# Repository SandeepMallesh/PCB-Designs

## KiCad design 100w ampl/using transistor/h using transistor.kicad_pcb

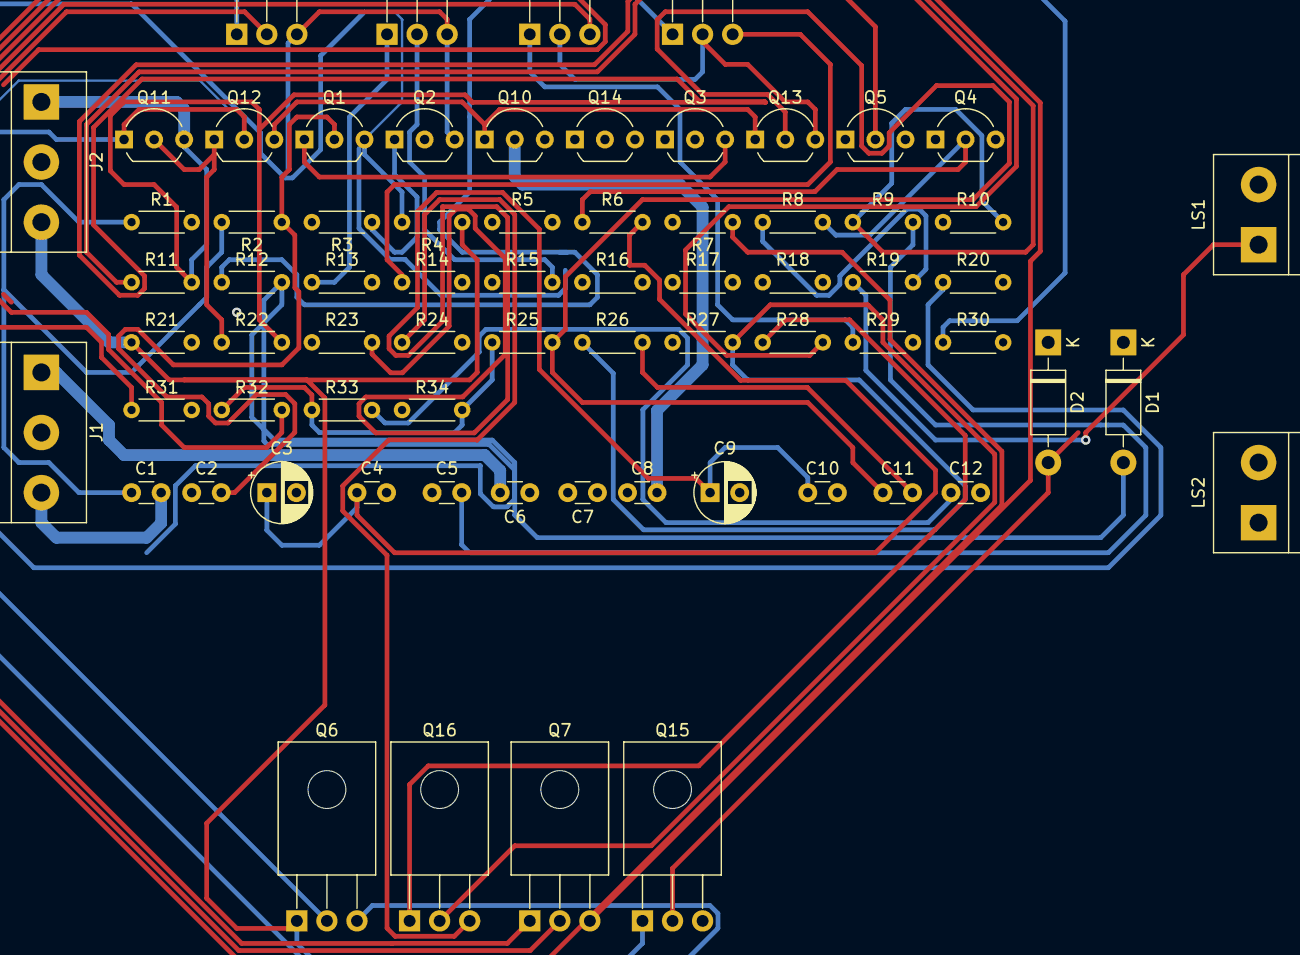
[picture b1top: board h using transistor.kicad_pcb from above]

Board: 2 copper layers, 70 parts (0 on the bottom side), 47 nets.

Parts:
C1, C6: 470n; C_Disc_D3.0mm_W1.6mm_P2.50mm
C2, C8: 470pf; C_Disc_D3.0mm_W1.6mm_P2.50mm
C3, C9: 47u; CP_Radial_D5.0mm_P2.50mm
C4, C7, C10, C12: 100n; C_Disc_D3.0mm_W1.6mm_P2.50mm
C5, C11: 100pf; C_Disc_D3.0mm_W1.6mm_P2.50mm
D1, D2: 1N4002; D_DO-41_SOD81_P10.16mm_Horizontal
J1: R G L; TerminalBlock_bornier-3_P5.08mm
J2: PWR; TerminalBlock_bornier-3_P5.08mm
LS1, LS2: Speaker; TerminalBlock_bornier-2_P5.08mm
Q1, Q3, Q4, Q10, Q12, Q13: MPSA43; TO-92_Inline_Wide
Q2, Q5, Q11, Q14: BC546; TO-92_Inline_Wide
Q6, Q15: MJE350; TO-126_Horizontal
Q7, Q16: MJE340; TO-126_Horizontal
Q8, Q17: IRFP244; TO-220-3_Horizontal
Q9, Q18: IRFP9240; TO-220-3_Horizontal
R1, R16: 47k; R_Axial_DIN0204_L3.6mm_D1.6mm_P5.08mm_Horizontal
R2, R18: 4.7k; R_Axial_DIN0204_L3.6mm_D1.6mm_P5.08mm_Horizontal
R3, R20: 22k; R_Axial_DIN0204_L3.6mm_D1.6mm_P5.08mm_Horizontal
R4, R21: 1k; R_Axial_DIN0204_L3.6mm_D1.6mm_P5.08mm_Horizontal
R5, R12, R13, R22, R29, R30: 330; R_Axial_DIN0204_L3.6mm_D1.6mm_P5.08mm_Horizontal
R6, R23: 1.5k; R_Axial_DIN0204_L3.6mm_D1.6mm_P5.08mm_Horizontal
R7, R24: 15k; R_Axial_DIN0204_L3.6mm_D1.6mm_P5.08mm_Horizontal
R8, R25: 33k; R_Axial_DIN0204_L3.6mm_D1.6mm_P5.08mm_Horizontal
R9, R26: 150k; R_Axial_DIN0204_L3.6mm_D1.6mm_P5.08mm_Horizontal
R10, R27: 390; R_Axial_DIN0204_L3.6mm_D1.6mm_P5.08mm_Horizontal
R11, R28: 39; R_Axial_DIN0204_L3.6mm_D1.6mm_P5.08mm_Horizontal
R14, R15, R31, R32: 0R33; R_Axial_DIN0204_L3.6mm_D1.6mm_P5.08mm_Horizontal
R17, R33: 10; R_Axial_DIN0204_L3.6mm_D1.6mm_P5.08mm_Horizontal
R19, R34: 220; R_Axial_DIN0204_L3.6mm_D1.6mm_P5.08mm_Horizontal

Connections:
GND: C2.1, C3.2, C4.2, C7.2, C8.1, C9.2, C10.2, C12.2, J1.2, J2.2, LS1.2, LS2.2, R1.2, R3.2, R7.2, R16.2, R20.2, R24.2
unnamed: C1.1, R1.1, R2.2
unnamed: C1.2, J1.3
unnamed: C2.2, Q1.2, R2.1
unnamed: C3.1, C4.1, R6.2
unnamed: C5.1, Q4.2, R6.1, R8.2
unnamed: C5.2, R9.2
unnamed: C6.1, R16.1, R18.2
unnamed: C6.2, J1.1
unnamed: C7.1, R17.2
unnamed: C8.2, Q10.2, R18.1
unnamed: C9.1, C10.1, R23.2
unnamed: C11.1, Q13.2, R23.1, R25.2
unnamed: C11.2, R26.2
unnamed: C12.1, R33.2
unnamed: D1.1, R10.1
unnamed: D1.2, Q6.2, R12.2
unnamed: D2.1, R27.1
unnamed: D2.2, Q15.2, R29.2
unnamed: LS1.1, R19.1
unnamed: LS2.1, R34.1
unnamed: Q1.1, Q3.3, Q4.1
unnamed: Q1.3, Q6.3, R4.2
unnamed: Q2.1, Q3.2, R3.1
unnamed: Q2.2, Q3.1, R5.1
unnamed: Q5.2, Q7.1, R11.1
unnamed: Q5.3, Q7.3, R7.1
unnamed: Q7.2, R9.1, R10.2, R13.2
unnamed: Q8.1, R12.1
unnamed: Q8.3, R14.1
unnamed: Q9.1, R13.1
unnamed: Q9.2, R15.2
unnamed: Q10.1, Q12.3, Q13.1
unnamed: Q10.3, Q15.3, R21.2
unnamed: Q11.1, Q12.2, R20.1
unnamed: Q11.2, Q12.1, R22.1
unnamed: Q14.2, Q16.1, R28.1
unnamed: Q14.3, Q16.3, R24.1
unnamed: Q16.2, R26.1, R27.2, R30.2
unnamed: Q17.1, R29.1
unnamed: Q17.3, R31.1
unnamed: Q18.1, R30.1
unnamed: Q18.2, R32.2
unnamed: R8.1, R14.2, R15.1, R17.1, R19.2
unnamed: R25.1, R31.2, R32.1, R33.1, R34.2
VCC: J2.3, Q4.3, Q6.1, Q8.2, Q13.3, Q15.1, Q17.2, R4.1, R21.1
VSS: J2.1, Q2.3, Q5.1, Q9.3, Q11.3, Q14.1, Q18.3, R5.2, R11.2, R22.2, R28.2

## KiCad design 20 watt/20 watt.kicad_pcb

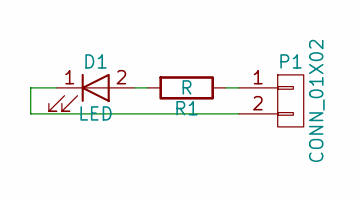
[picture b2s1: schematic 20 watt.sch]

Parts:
D1: LED; LED_D5.0mm_FlatTop
P1: CONN_01X02; SL-102-X-XX_1x02
R1: R; R_Axial_DIN0204_L3.6mm_D1.6mm_P5.08mm_Horizontal

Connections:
unnamed: D1.1 (K), P1.2
unnamed: D1.2 (A), R1.2
unnamed: P1.1, R1.1

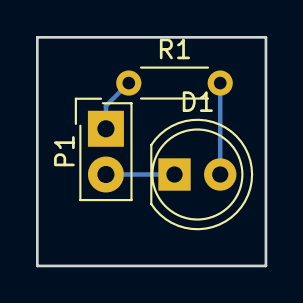
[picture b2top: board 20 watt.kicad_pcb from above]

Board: 2 copper layers, 12.7 x 12.7 mm, 3 parts (0 on the bottom side), 3 nets.

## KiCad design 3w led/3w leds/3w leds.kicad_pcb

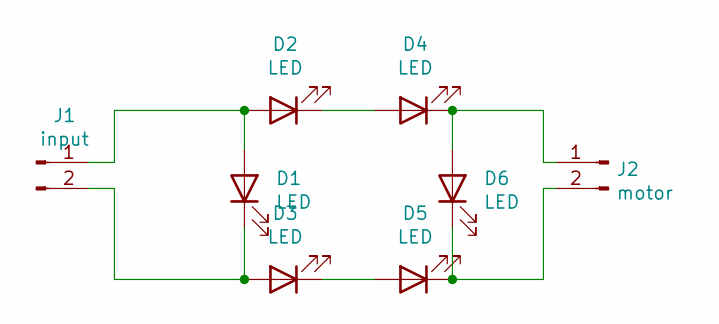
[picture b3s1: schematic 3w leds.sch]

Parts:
D1, D2, D3, D4, D5, D6: LED; LED_1W_3W_R8
J1: input; JWT_A3963_1x02_P3.96mm_Vertical
J2: motor; JWT_A3963_1x02_P3.96mm_Vertical

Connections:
unnamed: D1.1 (K), D3.2 (A), J1.2
unnamed: D1.2 (A), D2.2 (A), J1.1
unnamed: D2.1 (K), D4.2 (A)
unnamed: D3.1 (K), D5.2 (A)
unnamed: D4.1 (K), D6.2 (A), J2.1
unnamed: D5.1 (K), D6.1 (K), J2.2

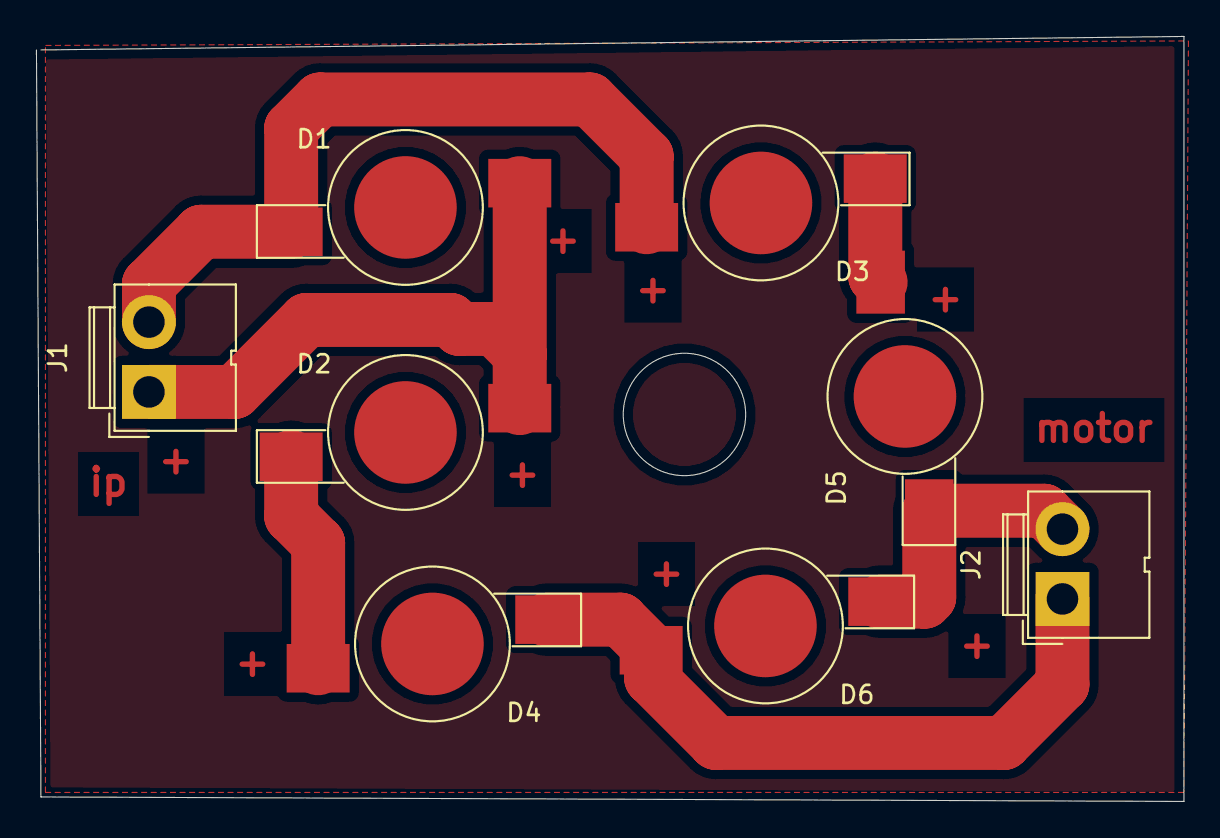
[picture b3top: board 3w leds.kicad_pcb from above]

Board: 2 copper layers, 63.8 x 42.5 mm, 8 parts (0 on the bottom side), 6 nets.

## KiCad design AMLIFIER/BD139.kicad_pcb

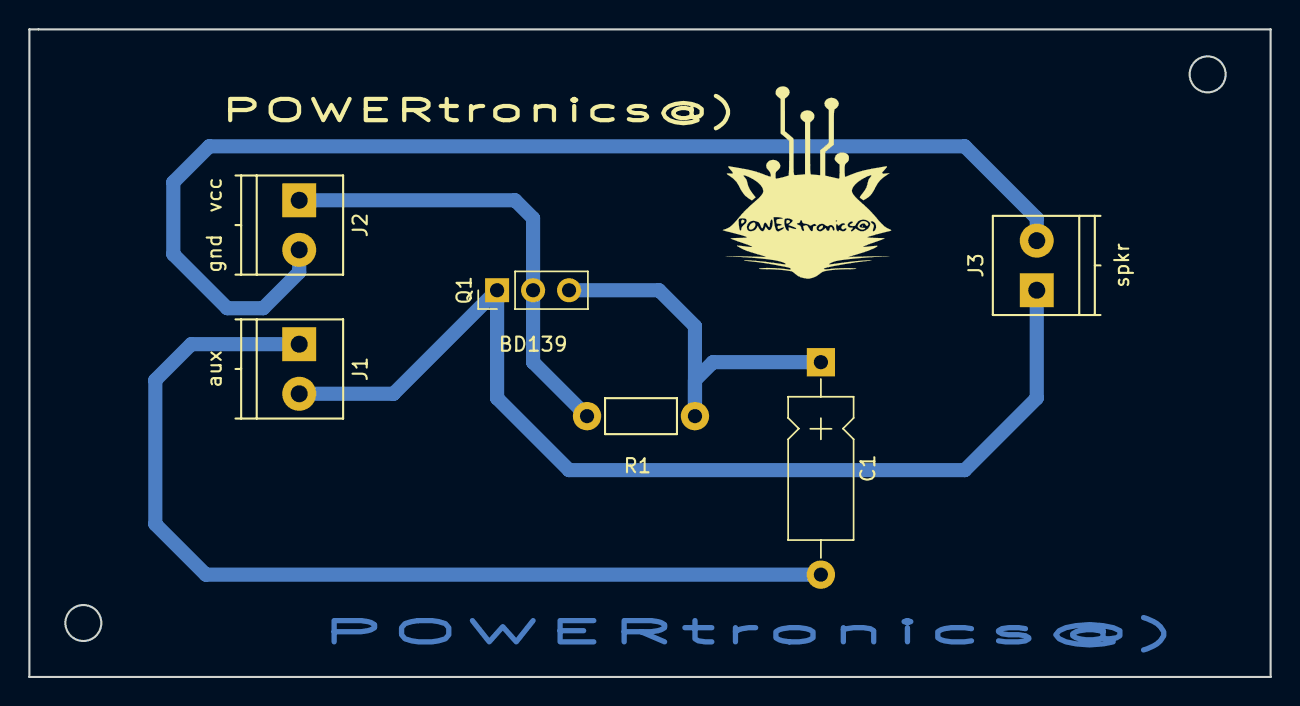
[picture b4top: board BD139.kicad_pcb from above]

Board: 2 copper layers, 87.6 x 45.7 mm, 6 parts (0 on the bottom side), 5 nets.

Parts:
C1: CP; CP_Axial_L10.0mm_D4.5mm_P15.00mm_Horizontal
J1: aux; TerminalBlock_Pheonix_PT-3.5mm_2pol
J2: gnd vcc; TerminalBlock_Pheonix_PT-3.5mm_2pol
J3: spkr; TerminalBlock_Pheonix_PT-3.5mm_2pol
Q1: BD139; PinHeader_1x03_P2.54mm_Vertical
R1: R; Resistor_Horizontal_RM7mm

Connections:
unnamed: C1.1, Q1.3, R1.1
unnamed: C1.2, J1.1
unnamed: J1.2, J3.1, Q1.1
unnamed: J2.1, Q1.2, R1.2
unnamed: J2.2, J3.2

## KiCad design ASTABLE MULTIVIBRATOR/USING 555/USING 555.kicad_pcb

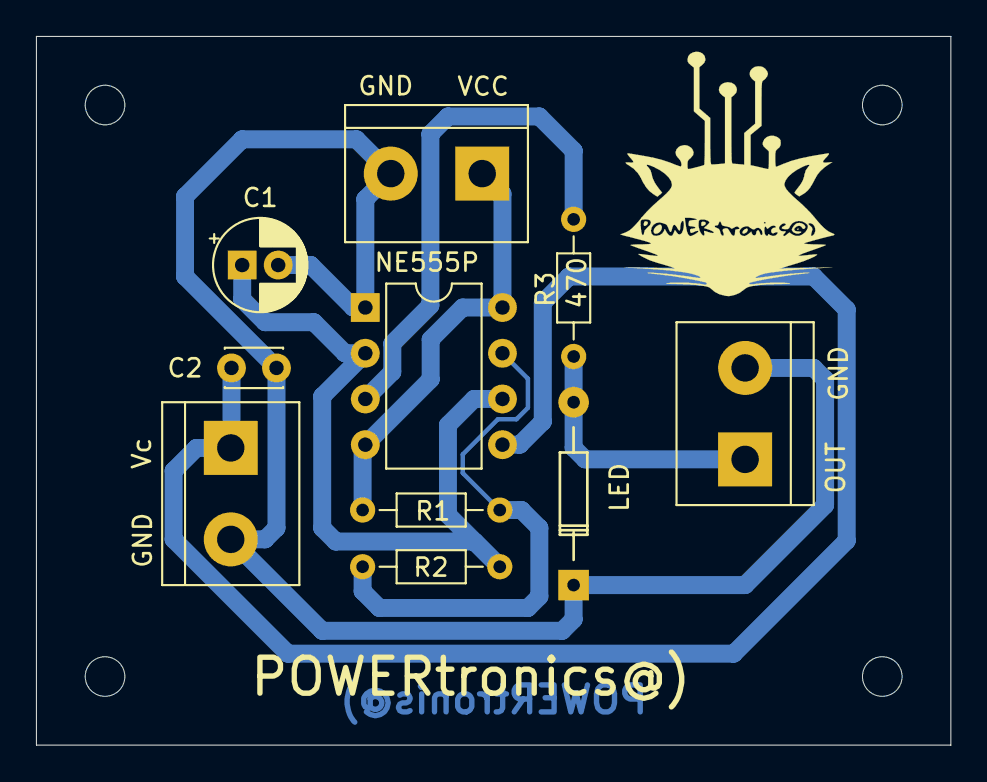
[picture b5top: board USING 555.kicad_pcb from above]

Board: 2 copper layers, 50.8 x 39.4 mm, 10 parts (0 on the bottom side), 7 nets.

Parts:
C1: CP; CP_Radial_D5.0mm_P2.00mm
C2: C; C_Disc_D3.0mm_W2.0mm_P2.50mm
GND1: Vc; TerminalBlock_bornier-2_P5.08mm
LED: LED; Diode_DO-35_SOD27_Horizontal_RM10
OUT: GND; TerminalBlock_bornier-2_P5.08mm
R1: R1; R_Axial_DIN0204_L3.6mm_D1.6mm_P7.62mm_Horizontal
R2: R2; R_Axial_DIN0204_L3.6mm_D1.6mm_P7.62mm_Horizontal
R3: 470; R_Axial_DIN0204_L3.6mm_D1.6mm_P7.62mm_Horizontal
U1: NE555P; DIP-8_W7.62mm
VCC: GND; TerminalBlock_bornier-2_P5.08mm

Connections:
GND: C1.2, C2.2, GND1.2, LED.1, OUT.2, U1.1, VCC.2
unnamed: C1.1, R2.2, U1.2, U1.6
unnamed: C2.1, GND1.1, U1.5
unnamed: LED.2, OUT.1, R3.1
unnamed: R1.2, R2.1, U1.7
unnamed: R3.2, U1.3
VCC: R1.1, U1.4, U1.8, VCC.1

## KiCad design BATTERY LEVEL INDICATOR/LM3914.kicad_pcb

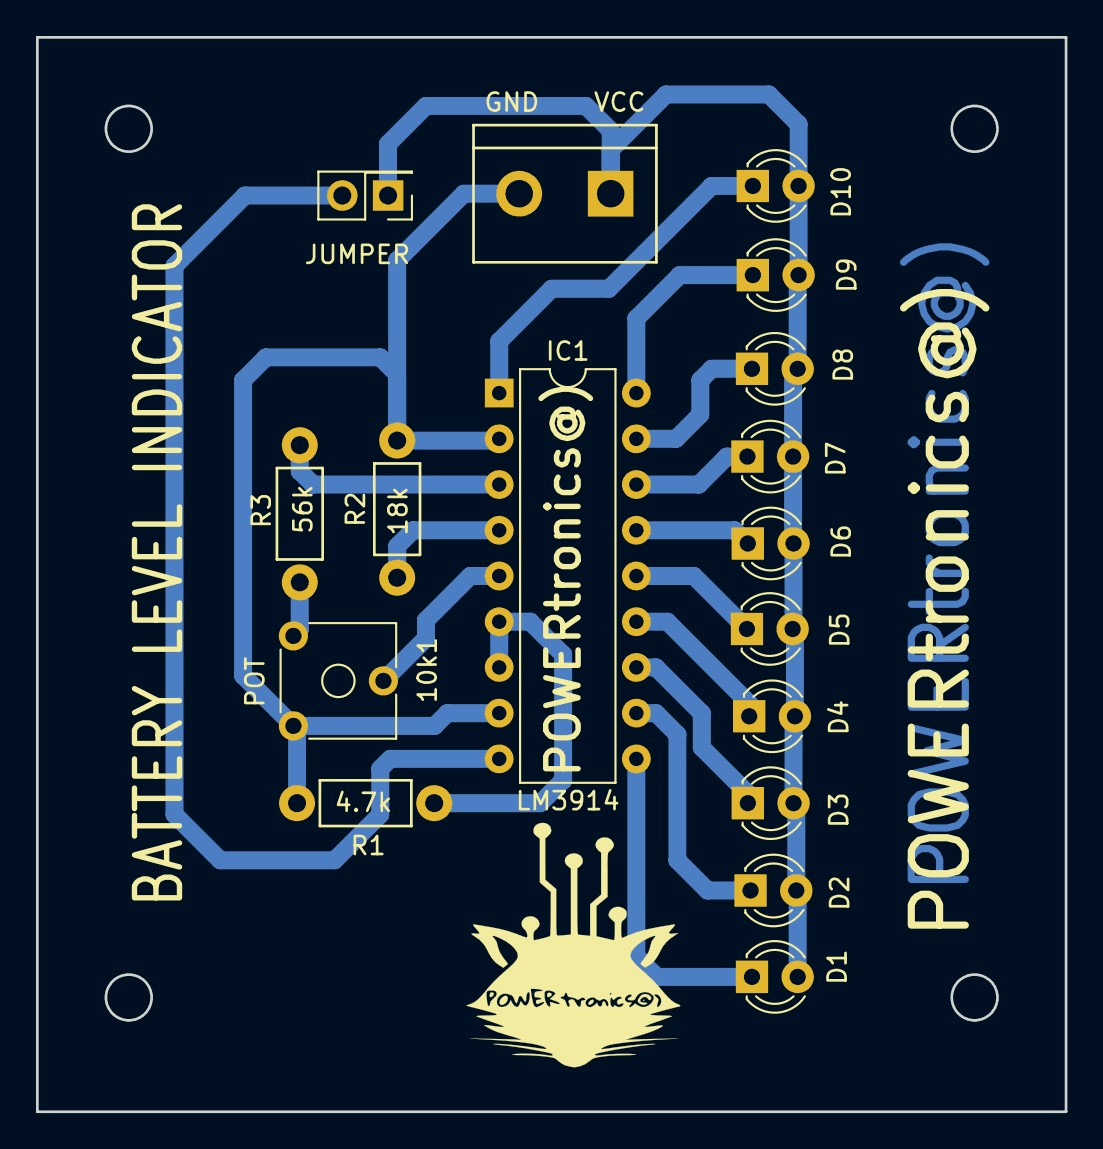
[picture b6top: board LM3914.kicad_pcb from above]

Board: 2 copper layers, 57.2 x 59.7 mm, 17 parts (0 on the bottom side), 18 nets.

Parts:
10k1: POT; Potentiometer_Trimmer_ACP_CA6v_Horizontal
D1, D2, D3, D4, D5, D6, D7, D8, D9, D10: LED; LED_D3.0mm_FlatTop
GND VCC: GND VCC; bornier2
IC1: LM3914; DIP-18_W7.62mm
JUMPER: Jumper_NO_Small; PinHeader_2x01_P2.54mm_Vertical
R1: 4.7k; Resistor_Horizontal_RM7mm
R2: 18k; Resistor_Horizontal_RM7mm
R3: 56k; Resistor_Horizontal_RM7mm

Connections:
unnamed: 10k1.1, GND VCC.2, IC1.2, IC1.8, R1.2, R2.2
unnamed: 10k1.2, IC1.5
unnamed: 10k1.3, R3.1
unnamed: D1.1, IC1.10
unnamed: D1.2, D2.2, D3.2, D4.2, D5.2, D6.2, D7.2, D8.2, D9.2, D10.2, GND VCC.1, JUMPER.1
unnamed: D2.1, IC1.11
unnamed: D3.1, IC1.12
unnamed: D4.1, IC1.13
unnamed: D5.1, IC1.14
unnamed: D6.1, IC1.15
unnamed: D7.1, IC1.16
unnamed: D8.1, IC1.17
unnamed: D9.1, IC1.18
unnamed: D10.1, IC1.1
unnamed: IC1.3, R3.2
unnamed: IC1.4, R2.1
unnamed: IC1.6, IC1.7, R1.1
unnamed: IC1.9, JUMPER.2

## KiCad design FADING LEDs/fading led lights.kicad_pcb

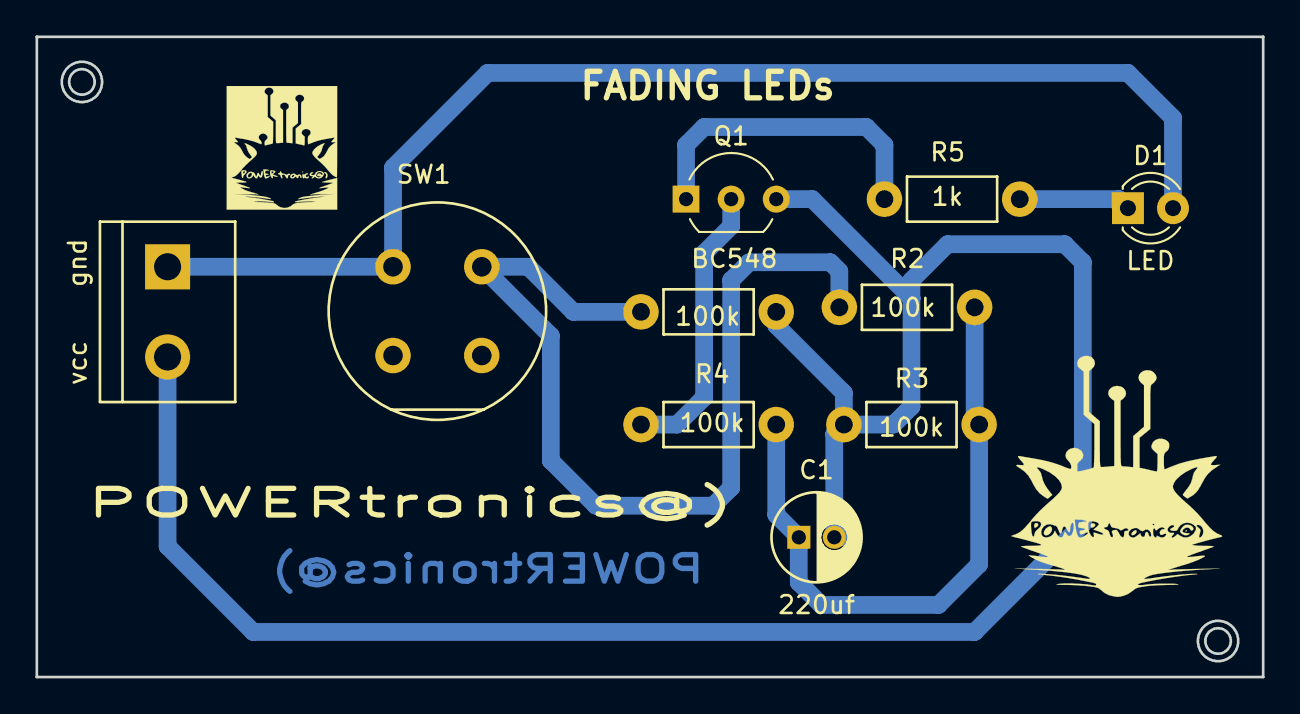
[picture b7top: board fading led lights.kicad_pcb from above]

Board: 2 copper layers, 69.1 x 36.1 mm, 10 parts (0 on the bottom side), 7 nets.

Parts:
C1: 220uf; C_Radial_D5_L11_P2
D1: LED; LED_D3.0mm
J1: vcc gnd; bornier2
Q1: BC548; TO-92_Inline_Wide
R1, R2, R3, R4: 100k; Resistor_Horizontal_RM7mm
R5: 1k; Resistor_Horizontal_RM7mm
SW1: SW_SPST; Push_E-Switch_KS01Q01

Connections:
unnamed: C1.1, R2.1, R3.1, R4.2
unnamed: C1.2, J1.2, Q1.3, R1.2, R3.2
unnamed: D1.1, R5.1
unnamed: D1.2, J1.1, SW1.1
unnamed: Q1.1, R5.2
unnamed: Q1.2, R4.1
unnamed: R1.1, R2.2, SW1.2
